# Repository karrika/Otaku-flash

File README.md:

# Otaku-flash
A single game flash card for Atari 2600, Atari 7800 and Atari 2600+

The logic in this card is based on Raspberrypi Pico

The startup of the Pico is too slow for a real Atari 7800. The way I
run the game is by:
- inserting the card when the power is off
- then I connect a powerbank to Pico's USB socket
- finally I power on the console
This allows the Pico to prepare everything before I power on
my Atari 7800 console. The schottky diode in the cart prevents the
powerbank to power on the console when the cart has power but the
console has not.

The new Atari 2600+ does not have a startup problem. But the Otaku cart
may draw too much current so I am also using the powerbank when the cart
is in the 2600+.

The cart has a 2600 connector and a 7800 connector. The 7800 connector can
be used for running all games. The 2600 connector only works for 2600 games.

Programming the cart:
- keep the button pressed while inserting the USB cable to the PC
- release the button
- drag a a game.uf2 file to the folder opened by the Otaku card

For converting a game into the uf2 format you need to install Raspberry Pico
tools with the SDK kit.

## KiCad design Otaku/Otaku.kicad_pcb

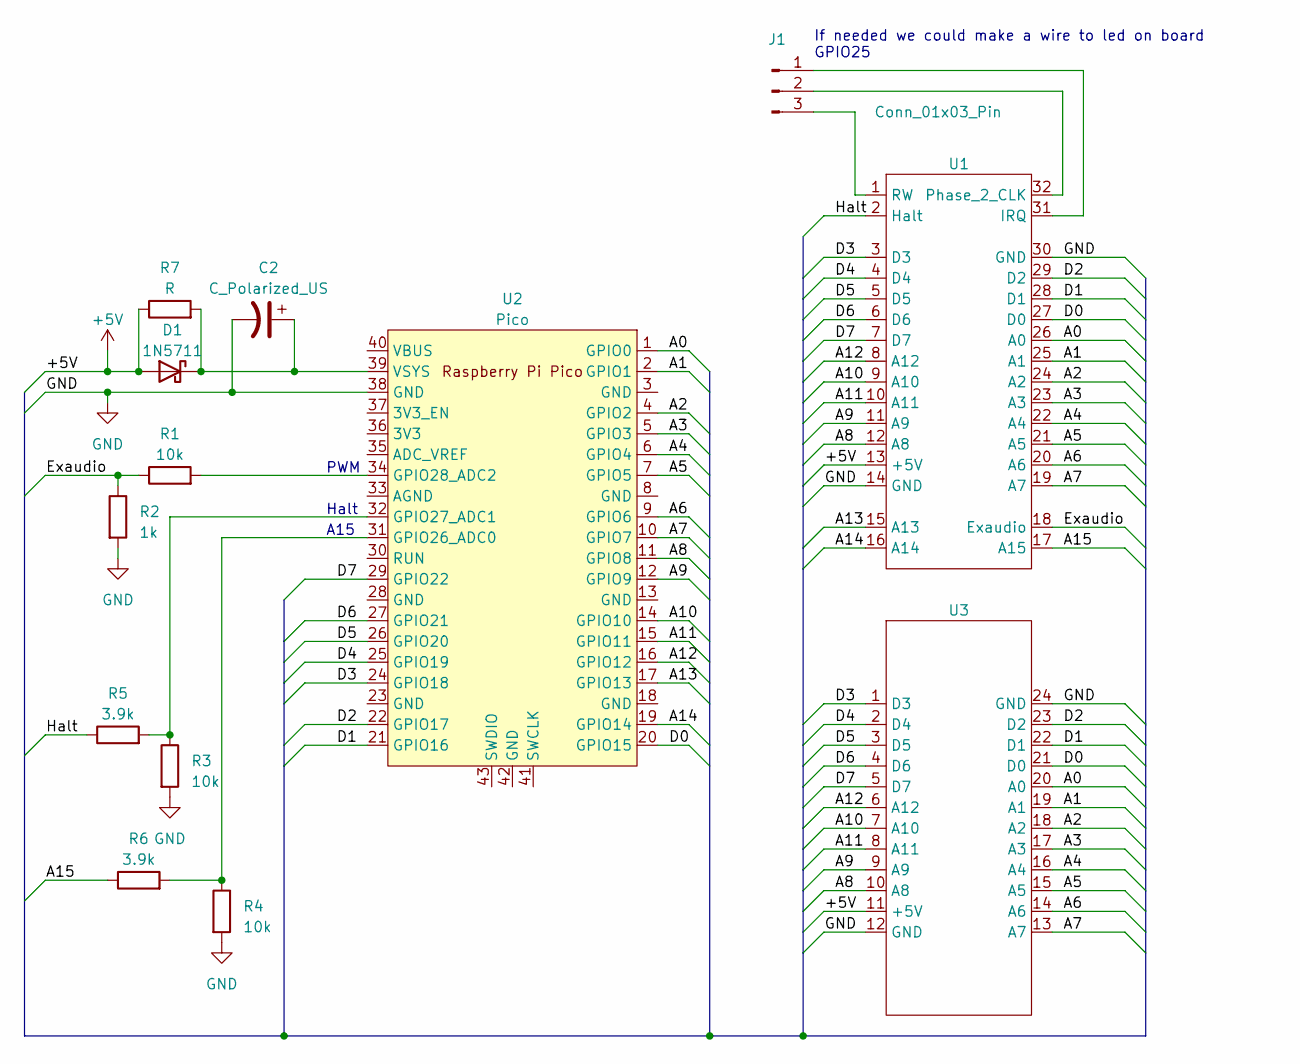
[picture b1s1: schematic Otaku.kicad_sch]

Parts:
C2: C_Polarized_US; CP_Axial_L10.0mm_D4.5mm_P15.00mm_Horizontal
D1: 1N5711; D_DO-35_SOD27_P7.62mm_Horizontal
J1: Conn_01x03_Pin; PinHeader_1x03_P2.54mm_Vertical
R1, R3, R4: 10k; R_1206_3216Metric_Pad1.30x1.75mm_HandSolder
R2: 1k; R_1206_3216Metric_Pad1.30x1.75mm_HandSolder
R5, R6: 3.9k; R_1206_3216Metric_Pad1.30x1.75mm_HandSolder
R7: R; R_1206_3216Metric_Pad1.30x1.75mm_HandSolder
U1: A7800
U2: Pico; RPi_Pico_SMD_TH
U3: A2600

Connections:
+5V: D1.2 (A), R7.1, U1.13 (+5V), U3.11 (+5V)
/A0: U1.26 (A0), U2.1 (GPIO0), U3.20 (A0)
/A1: U1.25 (A1), U2.2 (GPIO1), U3.19 (A1)
/A2: U1.24 (A2), U2.4 (GPIO2), U3.18 (A2)
/A3: U1.23 (A3), U2.5 (GPIO3), U3.17 (A3)
/A4: U1.22 (A4), U2.6 (GPIO4), U3.16 (A4)
/A5: U1.21 (A5), U2.7 (GPIO5), U3.15 (A5)
/A6: U1.20 (A6), U2.9 (GPIO6), U3.14 (A6)
/A7: U1.19 (A7), U2.10 (GPIO7), U3.13 (A7)
/A8: U1.12 (A8), U2.11 (GPIO8), U3.10 (A8)
/A9: U1.11 (A9), U2.12 (GPIO9), U3.9 (A9)
/A10: U1.9 (A10), U2.14 (GPIO10), U3.7 (A10)
/A11: U1.10 (A11), U2.15 (GPIO11), U3.8 (A11)
/A12: U1.8 (A12), U2.16 (GPIO12), U3.6 (A12)
/A13: U1.15 (A13), U2.17 (GPIO13)
/A14: U1.16 (A14), U2.19 (GPIO14)
/A15: R6.1, U1.17 (A15)
/D0: U1.27 (D0), U2.20 (GPIO15), U3.21 (D0)
/D1: U1.28 (D1), U2.21 (GPIO16), U3.22 (D1)
/D2: U1.29 (D2), U2.22 (GPIO17), U3.23 (D2)
/D3: U1.3 (D3), U2.24 (GPIO18), U3.1 (D3)
/D4: U1.4 (D4), U2.25 (GPIO19), U3.2 (D4)
/D5: U1.5 (D5), U2.26 (GPIO20), U3.3 (D5)
/D6: U1.6 (D6), U2.27 (GPIO21), U3.4 (D6)
/D7: U1.7 (D7), U2.29 (GPIO22), U3.5 (D7)
/Exaudio: R1.1, R2.1, U1.18 (Exaudio)
/Halt: R5.1, U1.2 (Halt)
GND: C2.2, R2.2, R3.2, R4.2, U1.14 (GND), U1.30 (GND), U2.38 (GND), U3.12 (GND), U3.24 (GND)
unnamed: C2.1, D1.1 (K), R7.2, U2.39 (VSYS)
unnamed: J1.1, U1.31 (IRQ)
unnamed: J1.2, U1.32 (Phase_2_CLK)
unnamed: J1.3, U1.1 (RW)
unnamed: R4.1, R6.2, U2.31 (GPIO26_ADC0)
unnamed: R3.1, R5.2, U2.32 (GPIO27_ADC1)
unnamed: R1.2, U2.34 (GPIO28_ADC2)

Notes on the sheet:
PWM
A15
Halt
If needed we could make a wire to led on board GPIO25

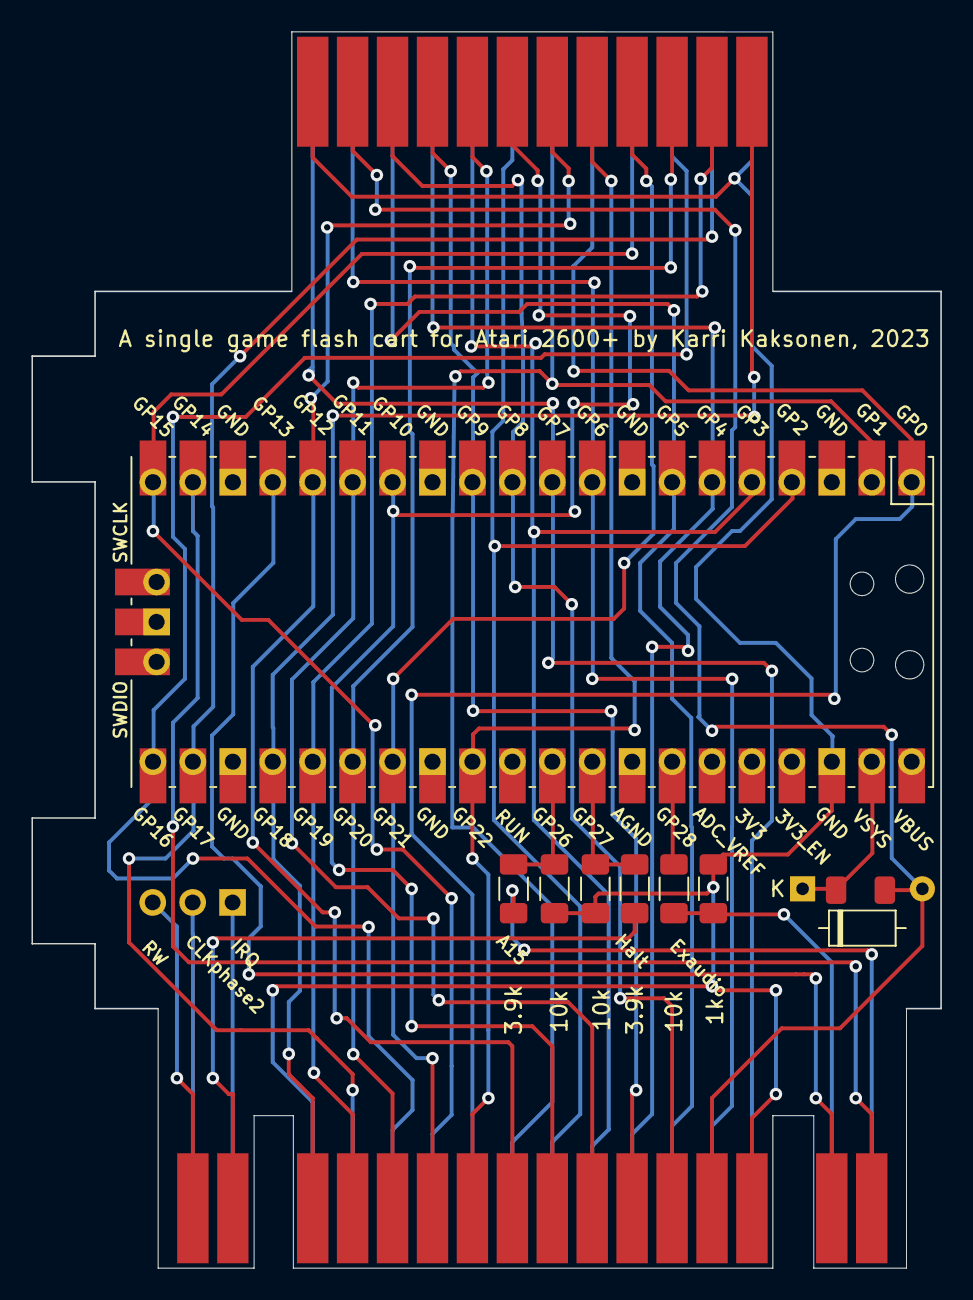
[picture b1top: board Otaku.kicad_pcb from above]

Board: 2 copper layers, 57.8 x 78.6 mm, 12 parts (0 on the bottom side), 35 nets.

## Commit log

2024-01-02 Add scripts to build rom.c
2024-01-02 Update README.md
    Add list of tested games
2024-01-02 Add KiCad 7 card design called Otaku
2024-01-02 Add F4 bankdswitching for Atari 2600 games
2024-01-02 Add example scripts for creating targets for the Otaku-flash card
2024-01-02 Add slow F6 build
2024-01-02 Fix typos
2024-01-03 Add image
2024-01-04 Add enclosure Blender model
2024-01-04 Add preliminary 3D printer files for the enclosure
2024-01-04 Update case
2024-01-04 Add build26rom2k.py and speed up
2024-01-04 Fix OtakuEnd
2024-01-09 Add Centipede for 7800. A 16k game
2024-01-09 streamline
2024-01-09 cleanup
2024-01-09 add bankswitching modes
2024-01-09 Speedup
2024-01-11 Use flash memory instead of RAM
2024-01-11 Use flash memory for game data
2024-01-11 Fix address bug
2024-01-11 Add script for 32k games for the 7800
2024-01-12 add cart type to game name
2024-01-14 Use 64k RAM buffer
2024-01-14 Add 48k build for Atari 7800 games
2024-01-15 Initialize GPIO25 as input for new RW pin
2024-01-16 Add type lookup from stella
2024-01-16 Add new bankswitch types
2024-01-17 Add build scripts
2024-01-17 Parse a78 header to see if we support the cart
2024-01-17 Update scripts
2024-01-17 Starts up game. Select mission. Then back to titel image
2024-01-17 Fix the logic for Absolute carts
2024-01-17 Fixed for real hw
2024-01-18 Add SUPER with EXFIX bankswitch format
2024-01-18 Add SuperGame EXRAM format
2024-01-18 Rename file to keep it logical
2024-01-18 Add comment
2024-01-18 Add HALT pin
2024-01-19 Add 8k game for 7800
2024-01-21 Add F6SC bankswitching
2024-01-21 Add F4SC bankswitching
2024-01-21 typo
2024-01-21 Fix bankswitching for SC carts
2024-01-21 Add runtests
2024-01-21 Add tests
2024-01-22 Add 7800 tests
2024-01-22 New cart cover design
2024-01-24 Add LICENSE
2024-01-24 Remove obsolete files
2024-01-24 Slightly modified top and screw holes
2024-01-24 Modify README
2024-01-24 Fix typo
2024-01-24 Make top a bit wider and stronger. Make screw holes on bottom smaller.
2024-02-15 Improve make process
2024-02-16 Add support for bin files without header
2024-02-16 Works on 2600+
2024-02-16 Separate exram
2024-02-16 Almost working on real 7800
2024-03-23 Add missing info78.py
2024-04-03 Add non-working FE mode
2024-04-03 Add wip stuff
2024-04-03 Use 400MHz
2024-04-03 Reduce clutter by processing only changed and stable data
